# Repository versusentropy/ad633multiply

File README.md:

# eurorack AD633 mulitply

## v2 

minor bugfixes - should workk exactly like my manually fixed version - but I have not ordered these exact gerbers. Please report, if you do.

### 4 to 3 matrix mixer with gain 2

### 3 outputs to AD633 (X * Y) / 10 + Z

### output gain 0..1.5

### 2 DC coupled outputs
one with fixed gain

### 2 AC coupled outputs

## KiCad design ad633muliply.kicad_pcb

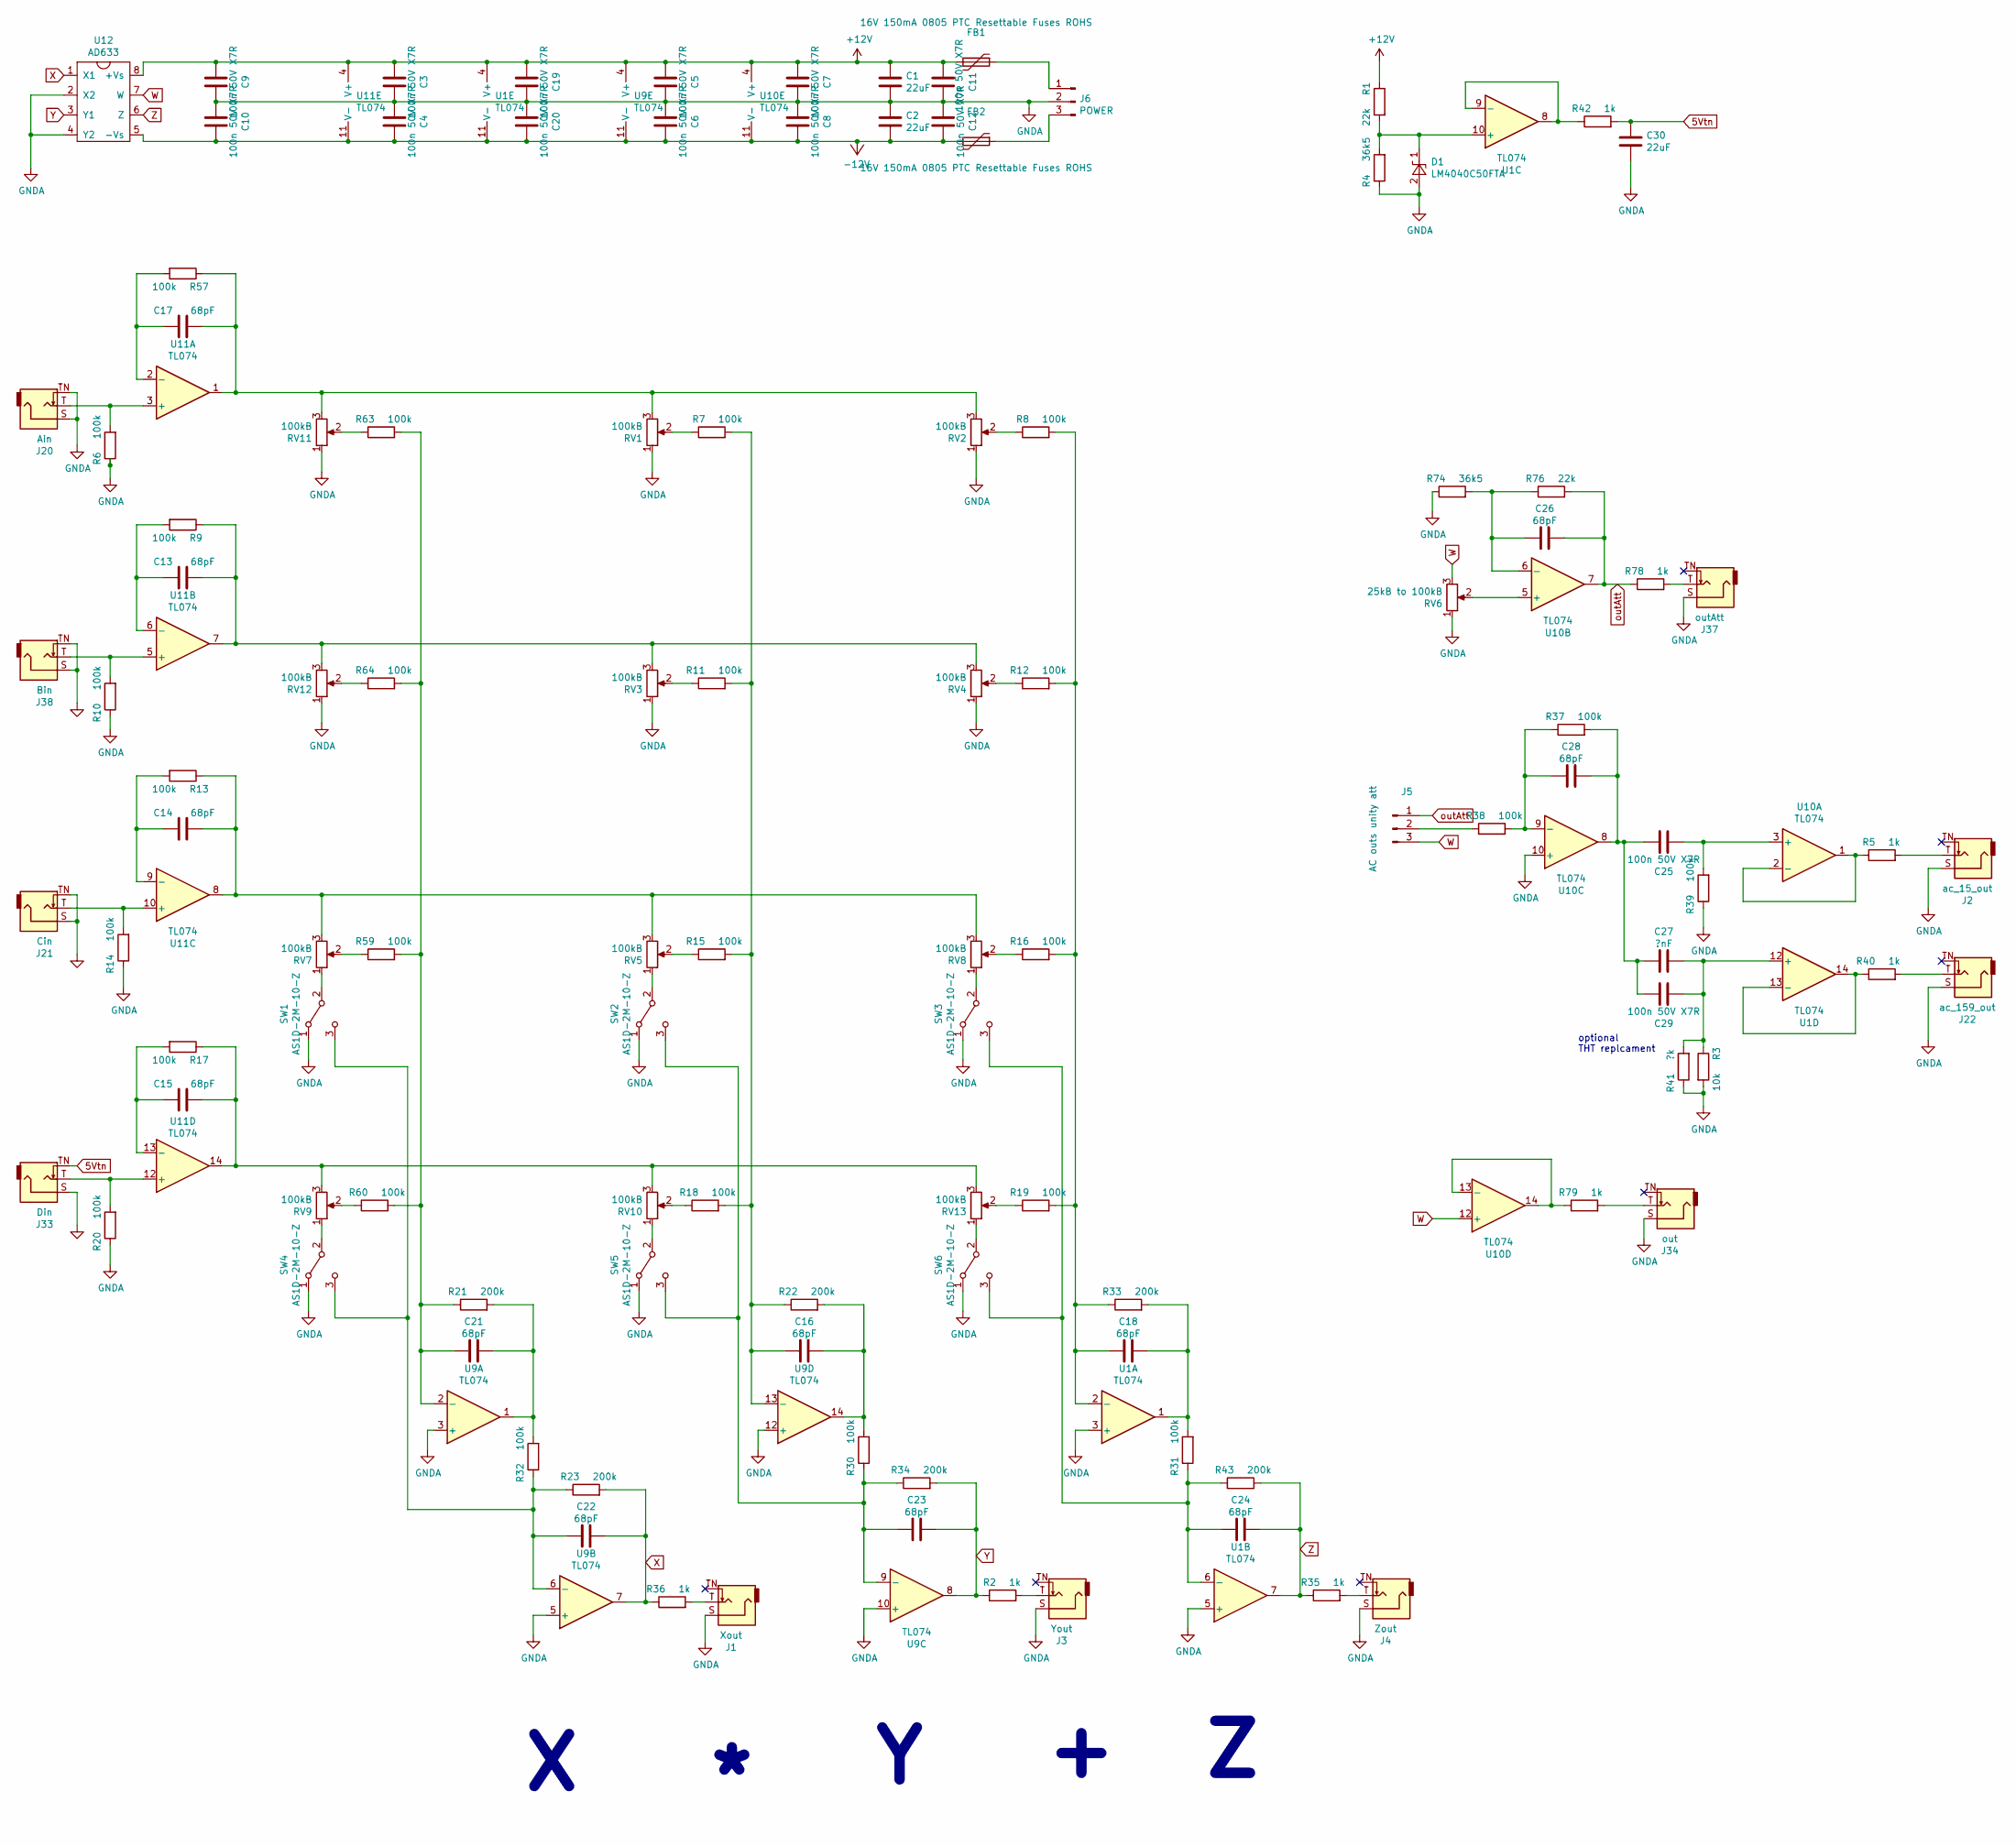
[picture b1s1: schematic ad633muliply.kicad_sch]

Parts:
C1, C2, C30: 22uF; C_0805_2012Metric; LCSC C45783
C3, C4, C5, C6, C7, C8, C9, C10, C11, C12, C19, C20, C25, C29: 100n 50V X7R; C_0402_1005Metric; LCSC C307331
C13, C14, C15, C16, C17, C18, C21, C22, C23, C24, C26, C28: 68pF; C_0402_1005Metric; LCSC C14441
C27: ?nF; CP_Radial_D6.3mm_P2.50mm
D1: LM4040C50FTA; SOT-23; LCSC C202168
FB1, FB2: 16V 150mA 0805 PTC Resettable Fuses ROHS; Fuse_0805_2012Metric; LCSC C30198
J1: Xout; Jack_3.5mm_QingPu_WQP-PJ398SM_Vertical_CircularHolesSMALL
J2: ac_15_out; Jack_3.5mm_QingPu_WQP-PJ398SM_Vertical_CircularHolesSMALL
J3: Yout; Jack_3.5mm_QingPu_WQP-PJ398SM_Vertical_CircularHolesSMALL
J4: Zout; Jack_3.5mm_QingPu_WQP-PJ398SM_Vertical_CircularHolesSMALL
J5: AC outs unity att; PinHeader_1x03_P2.54mm_Vertical
J6: POWER; eurorac_power
J20: Ain; Jack_3.5mm_QingPu_WQP-PJ398SM_Vertical_CircularHolesSMALL
J21: Cin; Jack_3.5mm_QingPu_WQP-PJ398SM_Vertical_CircularHolesSMALL
J22: ac_159_out; Jack_3.5mm_QingPu_WQP-PJ398SM_Vertical_CircularHolesSMALL
J33: Din; Jack_3.5mm_QingPu_WQP-PJ398SM_Vertical_CircularHolesSMALL
J34: out; Jack_3.5mm_QingPu_WQP-PJ398SM_Vertical_CircularHolesSMALL
J37: outAtt; Jack_3.5mm_QingPu_WQP-PJ398SM_Vertical_CircularHolesSMALL
J38: Bin; Jack_3.5mm_QingPu_WQP-PJ398SM_Vertical_CircularHolesSMALL
R1, R76: 22k; R_0603_1608Metric; LCSC C126297
R2, R5, R35, R36, R40, R42, R78, R79: 1k; R_0603_1608Metric; LCSC C21190
R3: 10k; R_0402_1005Metric; LCSC C98838
R4, R74: 36k5; R_0603_1608Metric; LCSC C51261
R6, R7, R8, R9, R10, R11, R12, R13, R14, R15, R16, R17, R18, R19, R20, R30, R31, R32, R37, R38, R39, R57, R59, R60, R63, R64: 100k; R_0402_1005Metric; LCSC C319963
R21, R22, R23, R33, R34, R43: 200k; R_0603_1608Metric; LCSC C319781
R41: ?k; R_Axial_DIN0207_L6.3mm_D2.5mm_P10.16mm_Horizontal
RV1, RV2, RV3, RV4, RV5, RV7, RV8, RV9, RV10, RV11, RV12, RV13: 100kB; RD901F-ALPHA-POT-T18
RV6: 25kB to 100kB; RD901F-ALPHA-POT-T18
SW1, SW2, SW3, SW4, SW5, SW6: AS1D-2M-10-Z; Mouser 229-AS1D-2M-10-Z
U1, U9, U10, U11: TL074; TSSOP-14_4.4x5mm_P0.65mm; LCSC C96507
U12: AD633; DIP-8_W7.62mm_Socket; Mouser 584-AD633ANZ

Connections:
5Vtn: C30.1, J33.TN, R42.2
+12V: C1.1, C3.2, C5.2, C7.2, C9.2, C11.2, C19.2, FB1.2, R1.1, U1.4 (V+), U9.4 (V+), U10.4 (V+), U11.4 (V+), U12.8 (+Vs)
-12V: C2.2, C4.1, C6.1, C8.1, C10.1, C12.1, C20.1, FB2.2, U1.11 (V-), U9.11 (V-), U10.11 (V-), U11.11 (V-), U12.5 (-Vs)
GNDA: C1.2, C2.1, C3.1, C4.2, C5.1, C6.2, C7.1, C8.2, C9.1, C10.2, C11.1, C12.2, C19.1, C20.2, C30.2, D1.2 (A), J1.S, J2.S, J3.S, J4.S, J6.2, J20.S, J20.TN, J21.S, J21.TN, J22.S, J33.S, J34.S, J37.S, J38.S, J38.TN, R3.2, R4.1, R6.1, R10.1, R14.1, R20.1, R39.1, R41.1, R74.1, RV1.1, RV2.1, RV3.1, RV4.1, RV6.1, RV11.1, RV12.1, SW1.1 (A), SW2.1 (A), SW3.1 (A), SW4.1 (A), SW5.1 (A), SW6.1 (A), U1.3 (+), U1.5 (+), U9.3 (+), U9.5 (+), U9.10 (+), U9.12 (+), U10.10 (+), U12.2 (X2), U12.4 (Y2)
unnamed: C13.1, R9.1, RV3.3, RV4.3, RV12.3, U11.7
unnamed: C13.2, R9.2, U11.6 (-)
unnamed: C14.1, R13.1, RV5.3, RV7.3, RV8.3, U11.8
unnamed: C14.2, R13.2, U11.9 (-)
unnamed: C15.1, R17.1, RV9.3, RV10.3, RV13.3, U11.14
unnamed: C15.2, R17.2, U11.13 (-)
unnamed: C16.1, R22.2, R30.2, U9.14
unnamed: C16.2, R7.2, R11.2, R15.2, R18.2, R22.1, U9.13 (-)
unnamed: C17.1, R57.1, RV1.3, RV2.3, RV11.3, U11.1
unnamed: C17.2, R57.2, U11.2 (-)
unnamed: C18.1, R31.2, R33.2, U1.1
unnamed: C18.2, R8.2, R12.2, R16.2, R19.2, R33.1, U1.2 (-)
unnamed: C21.1, R21.2, R32.2, U9.1
unnamed: C21.2, R21.1, R59.2, R60.2, R63.2, R64.2, U9.2 (-)
unnamed: C23.2, R30.1, R34.1, SW2.3 (C), SW5.3 (C), U9.9 (-)
unnamed: C25.1, C27.2, C28.1, C29.1, R37.2, U10.8
unnamed: C25.2, R39.2, U10.3 (+)
unnamed: C26.2, R74.2, R76.1, U10.6 (-)
unnamed: C27.1, C29.2, R3.1, R41.2, U1.12 (+)
unnamed: C28.2, R37.1, R38.2, U10.9 (-)
unnamed: D1.1 (K), R1.2, R4.2, U1.10 (+)
unnamed: FB1.1, J6.1
unnamed: FB2.1, J6.3
unnamed: J1.T, R36.2
unnamed: J2.T, R5.2
unnamed: J3.T, R2.2
unnamed: J4.T, R35.2
unnamed: J5.2, R38.1
unnamed: J20.T, R6.2, U11.3 (+)
unnamed: J21.T, R14.2, U11.10 (+)
unnamed: J22.T, R40.2
unnamed: J33.T, R20.2, U11.12 (+)
unnamed: J34.T, R79.2
unnamed: J37.T, R78.2
unnamed: J38.T, R10.2, U11.5 (+)
unnamed: R5.1, U10.1, U10.2 (-)
unnamed: R7.1, RV1.2
unnamed: R8.1, RV2.2
unnamed: R11.1, RV3.2
unnamed: R12.1, RV4.2
unnamed: R15.1, RV5.2
unnamed: R16.1, RV8.2
unnamed: R18.1, RV10.2
unnamed: R19.1, RV13.2
unnamed: R40.1, U1.13 (-), U1.14
unnamed: R42.1, U1.8, U1.9 (-)
unnamed: R59.1, RV7.2
unnamed: R60.1, RV9.2
unnamed: R63.1, RV11.2
unnamed: R64.1, RV12.2
unnamed: R79.1, U10.13 (-), U10.14
unnamed: RV5.1, SW2.2 (B)
unnamed: RV7.1, SW1.2 (B)
unnamed: RV8.1, SW3.2 (B)
unnamed: RV9.1, SW4.2 (B)
unnamed: RV10.1, SW5.2 (B)
unnamed: RV13.1, SW6.2 (B)
unnamed: C22.2, R23.1, R32.1, SW1.3 (C), SW4.3 (C), U9.6 (-)
unnamed: C24.2, R31.1, R43.1, SW3.3 (C), SW6.3 (C), U1.6 (-)
unnamed: RV6.2, U10.5 (+)
W: J5.3, RV6.3, U10.12 (+), U12.7 (W)
X: C22.1, R23.2, R36.1, U9.7, U12.1 (X1)
Y: C23.1, R2.1, R34.2, U9.8, U12.3 (Y1)
Z: C24.1, R35.1, R43.2, U1.7, U12.6 (Z)
outAtt: C26.1, J5.1, R76.2, R78.1, U10.7

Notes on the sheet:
optional THT replcament

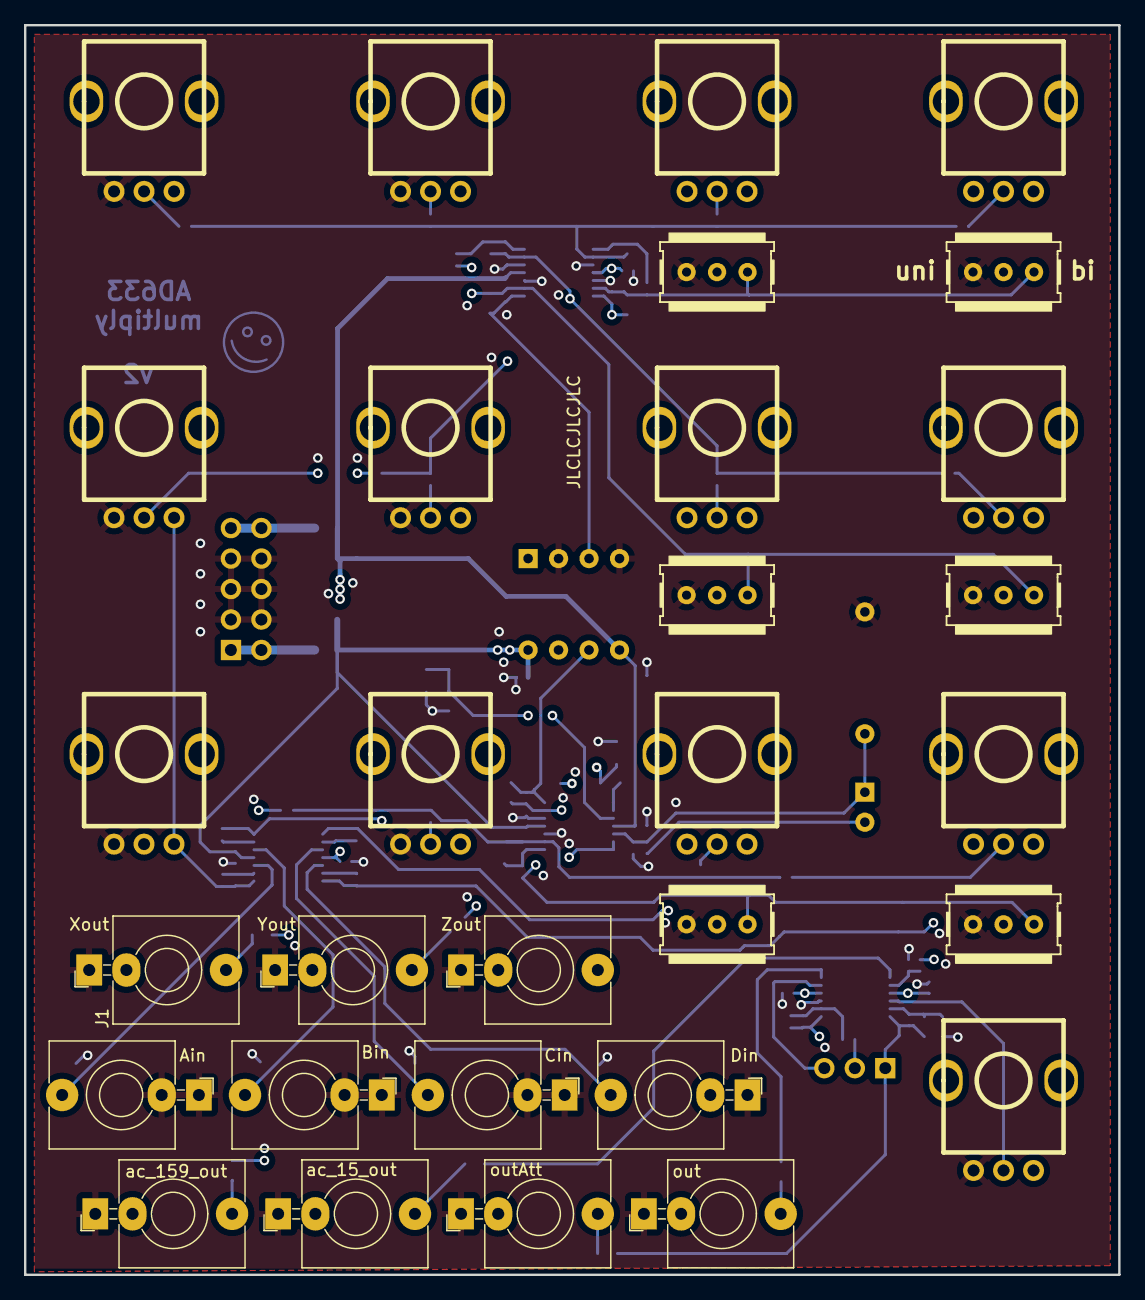
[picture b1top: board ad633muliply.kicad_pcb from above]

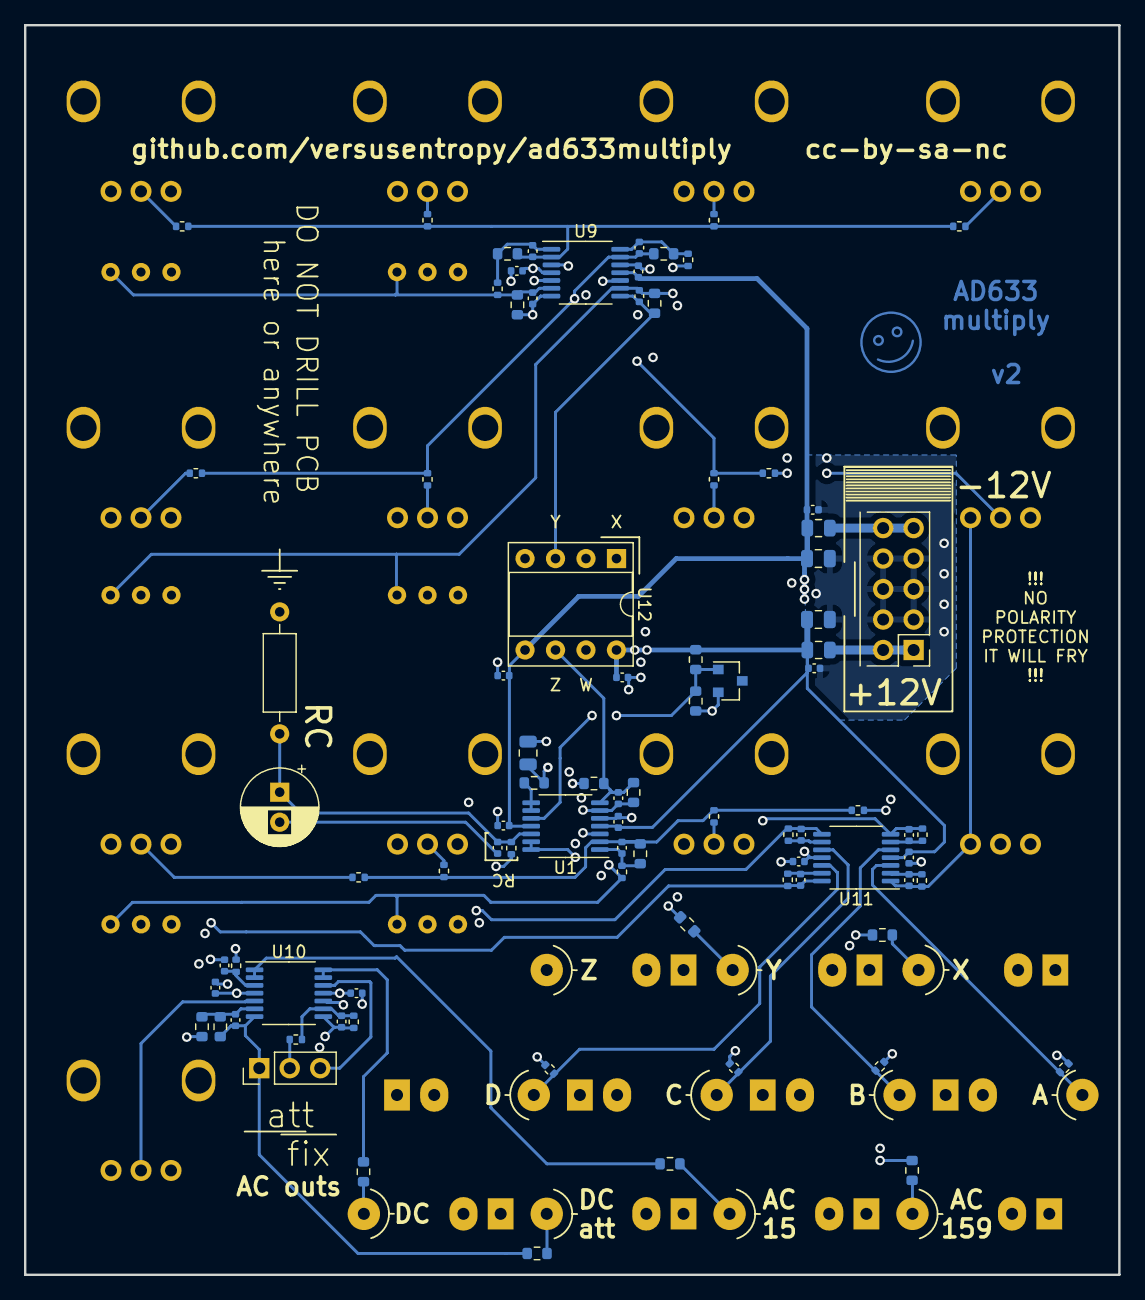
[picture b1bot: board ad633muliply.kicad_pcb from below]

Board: 4 copper layers, 91.2 x 104.1 mm, 116 parts (86 on the bottom side), 69 nets.

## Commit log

2022-02-23 init

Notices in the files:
ad633muliply.kicad_pcb:
github.com/versusentropy/ad633multiply cc-by-sa-nc
